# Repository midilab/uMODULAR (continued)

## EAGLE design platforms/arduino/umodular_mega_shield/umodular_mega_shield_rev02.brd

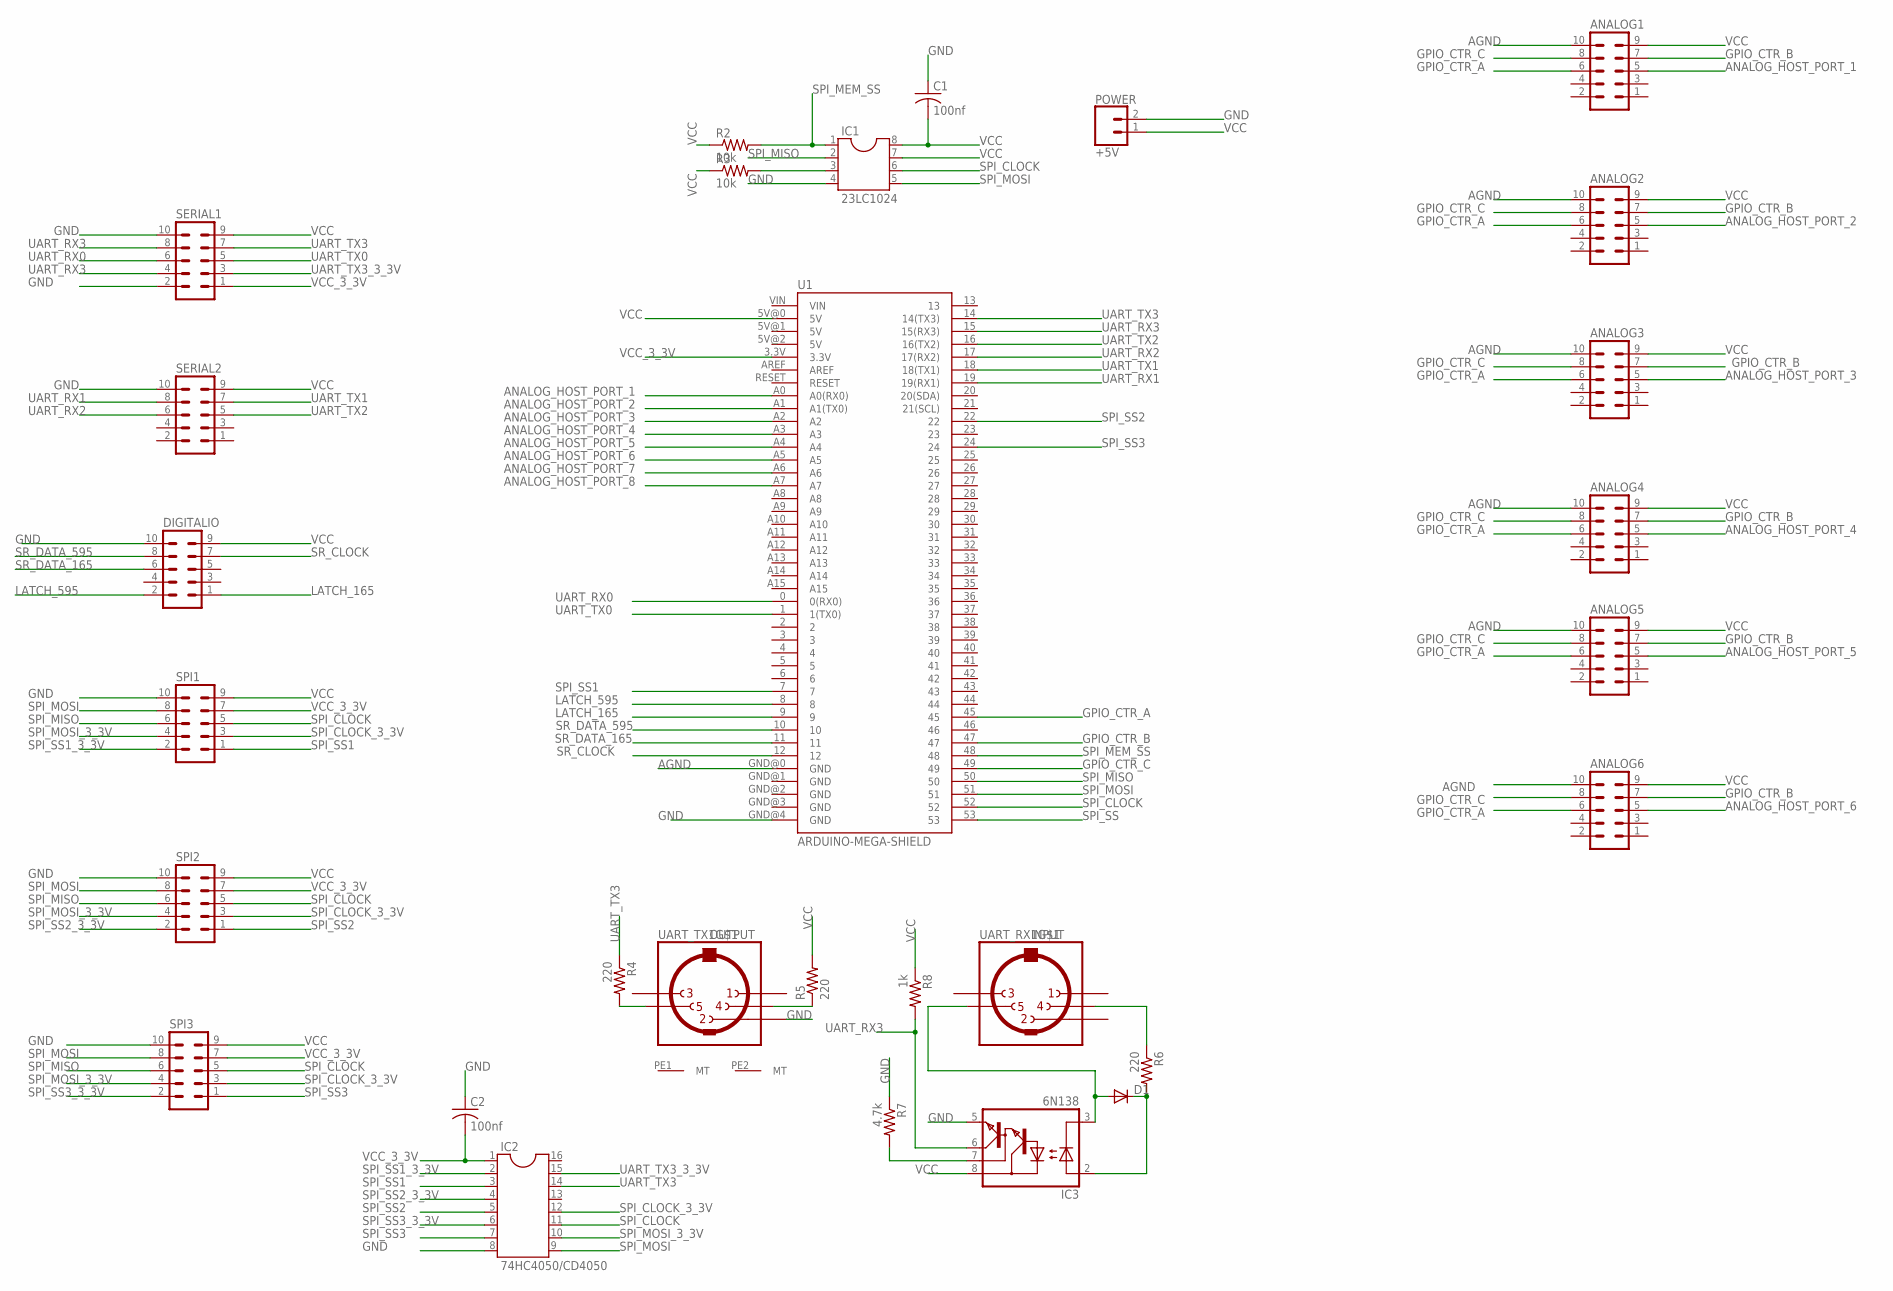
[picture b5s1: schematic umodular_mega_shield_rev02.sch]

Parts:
ANALOG1, ANALOG2, ANALOG3, ANALOG4, ANALOG5, ANALOG6: MA05-2
C1, C2: 100nf; C050-024X044
D1: 1N4148DO35-7; DO35-7
DIGITALIO: MA05-2
IC1: 23LC1024; DIL08
IC2: 74HC4050/CD4050; DIL16
IC3: 6N138; DIL08
POWER: +5V; 1X02_LOCK_LONGPADS
R2, R3: 10k; 0204/7@1
R4, R5, R6: 220; 0204/7@1
R7: 4.7k; 0204/7@1
R8: 1k; 0204/7@1
SERIAL1, SERIAL2: MA05-2
SPI1, SPI2, SPI3: MA05-2
U1: ARDUINO-MEGA-SHIELD; ARDUINO_MEGA@1
UART_RX1: INPUT; CP-2350
UART_TX1: OUTPUT; CP-2350

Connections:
AGND: ANALOG1.10, ANALOG2.10, ANALOG3.10, ANALOG4.10, ANALOG5.10, ANALOG6.10, U1.GND@0 (GND)
ANALOG_HOST_PORT_1: ANALOG1.5, U1.A0 (A0(RX0))
ANALOG_HOST_PORT_2: ANALOG2.5, U1.A1 (A1(TX0))
ANALOG_HOST_PORT_3: ANALOG3.5, U1.A2
ANALOG_HOST_PORT_4: ANALOG4.5, U1.A3
ANALOG_HOST_PORT_5: ANALOG5.5, U1.A4
ANALOG_HOST_PORT_6: ANALOG6.5, U1.A5
ANALOG_HOST_PORT_7: U1.A6
ANALOG_HOST_PORT_8: U1.A7
GND: C1.1, C2.1, DIGITALIO.10, IC1.4, IC2.8, IC3.5 (GND), POWER.2, R7.1, SERIAL1.2, SERIAL1.10, SERIAL2.10, SPI1.10, SPI2.10, SPI3.10, U1.GND@4 (GND), UART_TX1.2
GPIO_CTR_A: ANALOG1.6, ANALOG2.6, ANALOG3.6, ANALOG4.6, ANALOG5.6, ANALOG6.6, U1.45
GPIO_CTR_B: ANALOG1.7, ANALOG2.7, ANALOG3.7, ANALOG4.7, ANALOG5.7, ANALOG6.7, U1.47
GPIO_CTR_C: ANALOG1.8, ANALOG2.8, ANALOG3.8, ANALOG4.8, ANALOG5.8, ANALOG6.8, U1.49
LATCH_165: DIGITALIO.1, U1.9
LATCH_595: DIGITALIO.2, U1.8
unnamed: R5.1, UART_TX1.4
unnamed: R4.2, UART_TX1.5
unnamed: IC1.3, R3.2
unnamed: R6.1, UART_RX1.4
unnamed: D1.C, IC3.2 (A), R6.2
unnamed: D1.A, IC3.3 (C), UART_RX1.5
unnamed: IC3.7 (VB), R7.2
SPI_CLOCK: IC1.6, IC2.11, SPI1.5, SPI2.5, SPI3.5, U1.52
SPI_CLOCK_3_3V: IC2.12, SPI1.3, SPI2.3, SPI3.3
SPI_MEM_SS: IC1.1, R2.2, U1.48
SPI_MISO: IC1.2, SPI1.6, SPI2.6, SPI3.6, U1.50
SPI_MOSI: IC1.5, IC2.9, SPI1.8, SPI2.8, SPI3.8, U1.51
SPI_MOSI_3_3V: IC2.10, SPI1.4, SPI2.4, SPI3.4
SPI_SS: U1.53
SPI_SS1: IC2.3, SPI1.1, U1.7
SPI_SS1_3_3V: IC2.2, SPI1.2
SPI_SS2: IC2.5, SPI2.1, U1.22
SPI_SS2_3_3V: IC2.4, SPI2.2
SPI_SS3: IC2.7, SPI3.1, U1.24
SPI_SS3_3_3V: IC2.6, SPI3.2
SR_CLOCK: DIGITALIO.7, U1.12
SR_DATA_165: DIGITALIO.6, U1.11
SR_DATA_595: DIGITALIO.8, U1.10
UART_RX0: SERIAL1.6, U1.0 (0(RX0))
UART_RX1: SERIAL2.8, U1.19 (19(RX1))
UART_RX2: SERIAL2.6, U1.17 (17(RX2))
UART_RX3: IC3.6 (VO), R8.2, SERIAL1.4, SERIAL1.8, U1.15 (15(RX3))
UART_TX0: SERIAL1.5, U1.1 (1(TX0))
UART_TX1: SERIAL2.7, U1.18 (18(TX1))
UART_TX2: SERIAL2.5, U1.16 (16(TX2))
UART_TX3: IC2.14, R4.1, SERIAL1.7, U1.14 (14(TX3))
UART_TX3_3_3V: IC2.15, SERIAL1.3
VCC: ANALOG1.9, ANALOG2.9, ANALOG3.9, ANALOG4.9, ANALOG5.9, ANALOG6.9, C1.2, DIGITALIO.9, IC1.7, IC1.8, IC3.8 (VCC), POWER.1, R2.1, R3.1, R5.2, R8.1, SERIAL1.9, SERIAL2.9, SPI1.9, SPI2.9, SPI3.9, U1.5V@0 (5V)
VCC_3_3V: C2.2, IC2.1, SERIAL1.1, SPI1.7, SPI2.7, SPI3.7, U1.3.3V

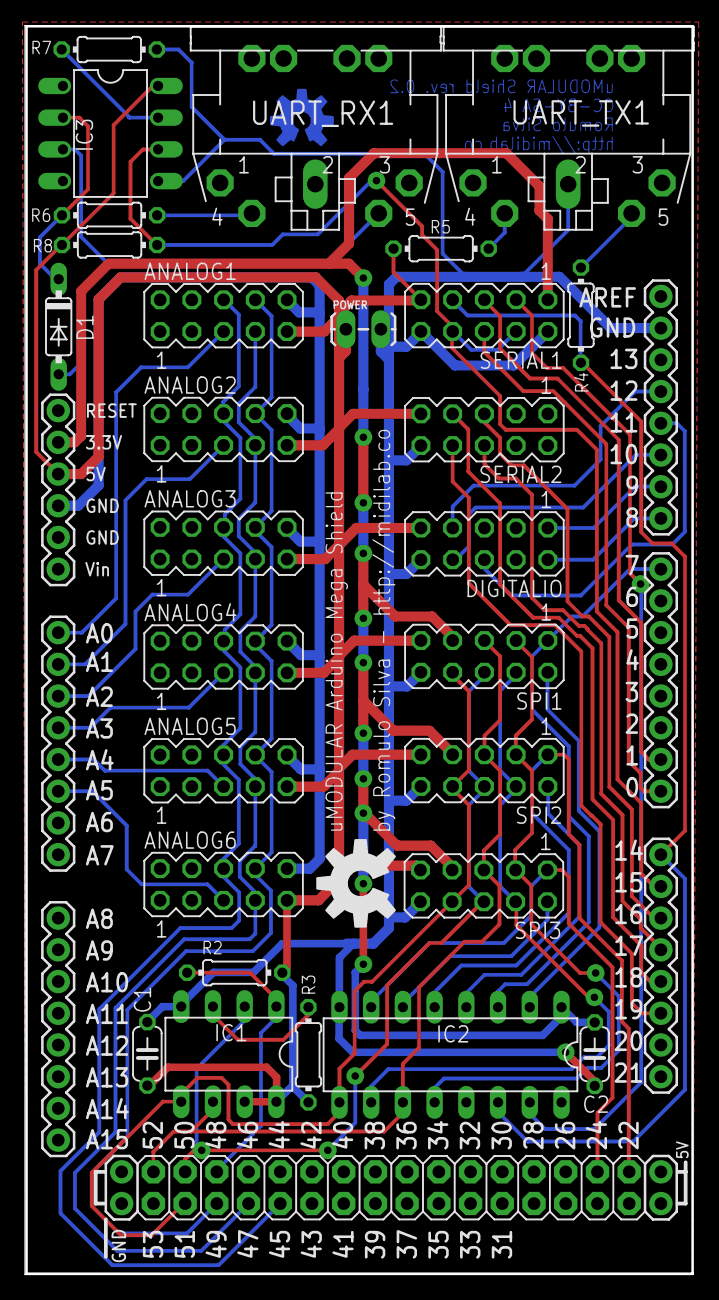
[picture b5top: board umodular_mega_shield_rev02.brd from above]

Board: 2 copper layers, 53.5 x 100.0 mm, 31 parts (0 on the bottom side), 46 nets.

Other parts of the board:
U$1: OSHW-LOGO-M
U$5: OSHW-LOGO-L

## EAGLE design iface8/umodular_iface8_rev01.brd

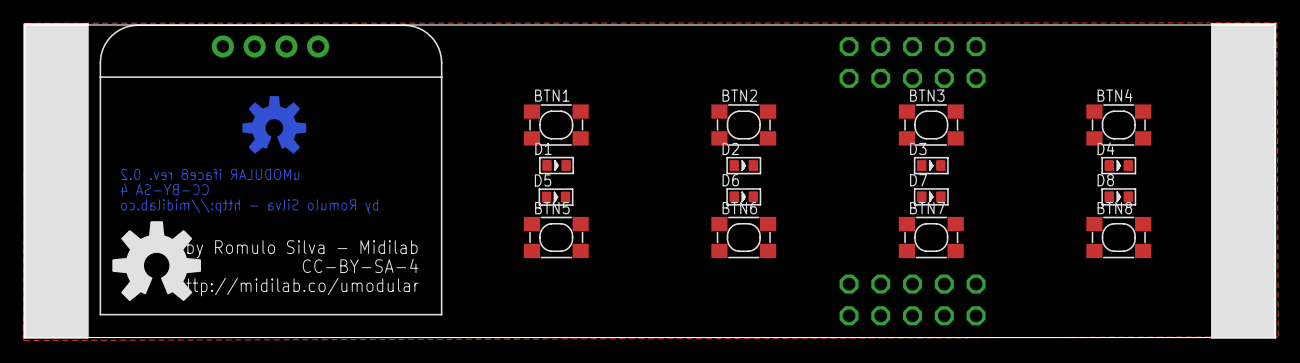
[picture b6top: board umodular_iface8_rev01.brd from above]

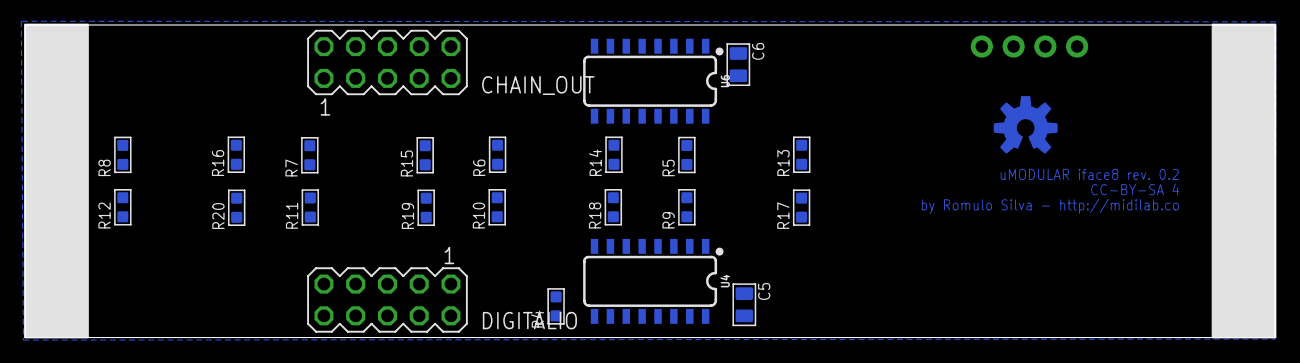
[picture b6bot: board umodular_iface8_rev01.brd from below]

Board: 2 copper layers, 100.0 x 25.0 mm, 44 parts (23 on the bottom side), 35 nets, no tracks yet.

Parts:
BTN1, BTN2, BTN3, BTN4, BTN5, BTN6, BTN7, BTN8: DHT-4235A; SW4-SMD-4.2X3.2X2.5MM
C5, C6: 100nf; C0805
CHAIN_OUT: MA05-2
D1, D2, D3, D4, D5, D6, D7, D8: RED-0603; LED-0603
DIGITALIO: MA05-2
R4, R5, R6, R7, R8, R9, R10, R11, R12: 10K; R0603
R13, R14, R15, R16, R17, R18, R19, R20: 220R; R0603
U4: SN74HC165DR; SO16
U6: SN74HC595D; SO16
U$1: OSHW-LOGO-M
U$2, U$4: OLED_0.96_I2C
U$3: OLED_0.96_I2C
U$5: OSHW-LOGO-L

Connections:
GND: BTN1.4, BTN2.4, BTN3.4, BTN4.4, BTN5.4, BTN6.4, BTN7.4, BTN8.4, C5.1, C6.2, CHAIN_OUT.10, D1.-, D2.-, D3.-, D4.-, D5.-, D6.-, D7.-, D8.-, DIGITALIO.10, U4.8, U4.15, U6.8, U6.13, U$3.GND
I2C_SCL: CHAIN_OUT.4, DIGITALIO.4, U$3.SCL
I2C_SDA: CHAIN_OUT.3, DIGITALIO.3, U$3.SDA
unnamed: BTN8.1, R12.1, U4.6
unnamed: R13.1, U6.15
unnamed: R14.1, U6.1
unnamed: R15.1, U6.2
unnamed: R16.1, U6.3
unnamed: R17.1, U6.4
unnamed: R18.1, U6.5
unnamed: BTN7.1, R11.1, U4.5
unnamed: BTN6.1, R10.1, U4.4
unnamed: BTN5.1, R9.1, U4.3
unnamed: BTN4.1, R8.1, U4.14
unnamed: BTN3.1, R7.1, U4.13
unnamed: BTN2.1, R6.1, U4.12
unnamed: BTN1.1, R5.1, U4.11
unnamed: R19.1, U6.6
unnamed: R20.1, U6.7
unnamed: D1.+, R13.2
unnamed: D2.+, R14.2
unnamed: D3.+, R15.2
unnamed: D4.+, R16.2
unnamed: D5.+, R17.2
unnamed: D6.+, R18.2
unnamed: D7.+, R19.2
unnamed: D8.+, R20.2
SPI_CLOCK: CHAIN_OUT.7, DIGITALIO.7, U4.2, U6.11
SPI_CS1: CHAIN_OUT.1, DIGITALIO.1, U4.1
SPI_CS2: CHAIN_OUT.2, DIGITALIO.2, U6.12
SPI_MISO: DIGITALIO.6, U4.9
SPI_MISO_CHAIN: CHAIN_OUT.6, R4.1, U4.10
SPI_MOSI: DIGITALIO.8, U6.14
SPI_MOSI_CHAIN: CHAIN_OUT.8, U6.9
VCC: C5.2, C6.1, CHAIN_OUT.9, DIGITALIO.9, R4.2, R5.2, R6.2, R7.2, R8.2, R9.2, R10.2, R11.2, R12.2, U4.16, U6.10, U6.16, U$3.VCC

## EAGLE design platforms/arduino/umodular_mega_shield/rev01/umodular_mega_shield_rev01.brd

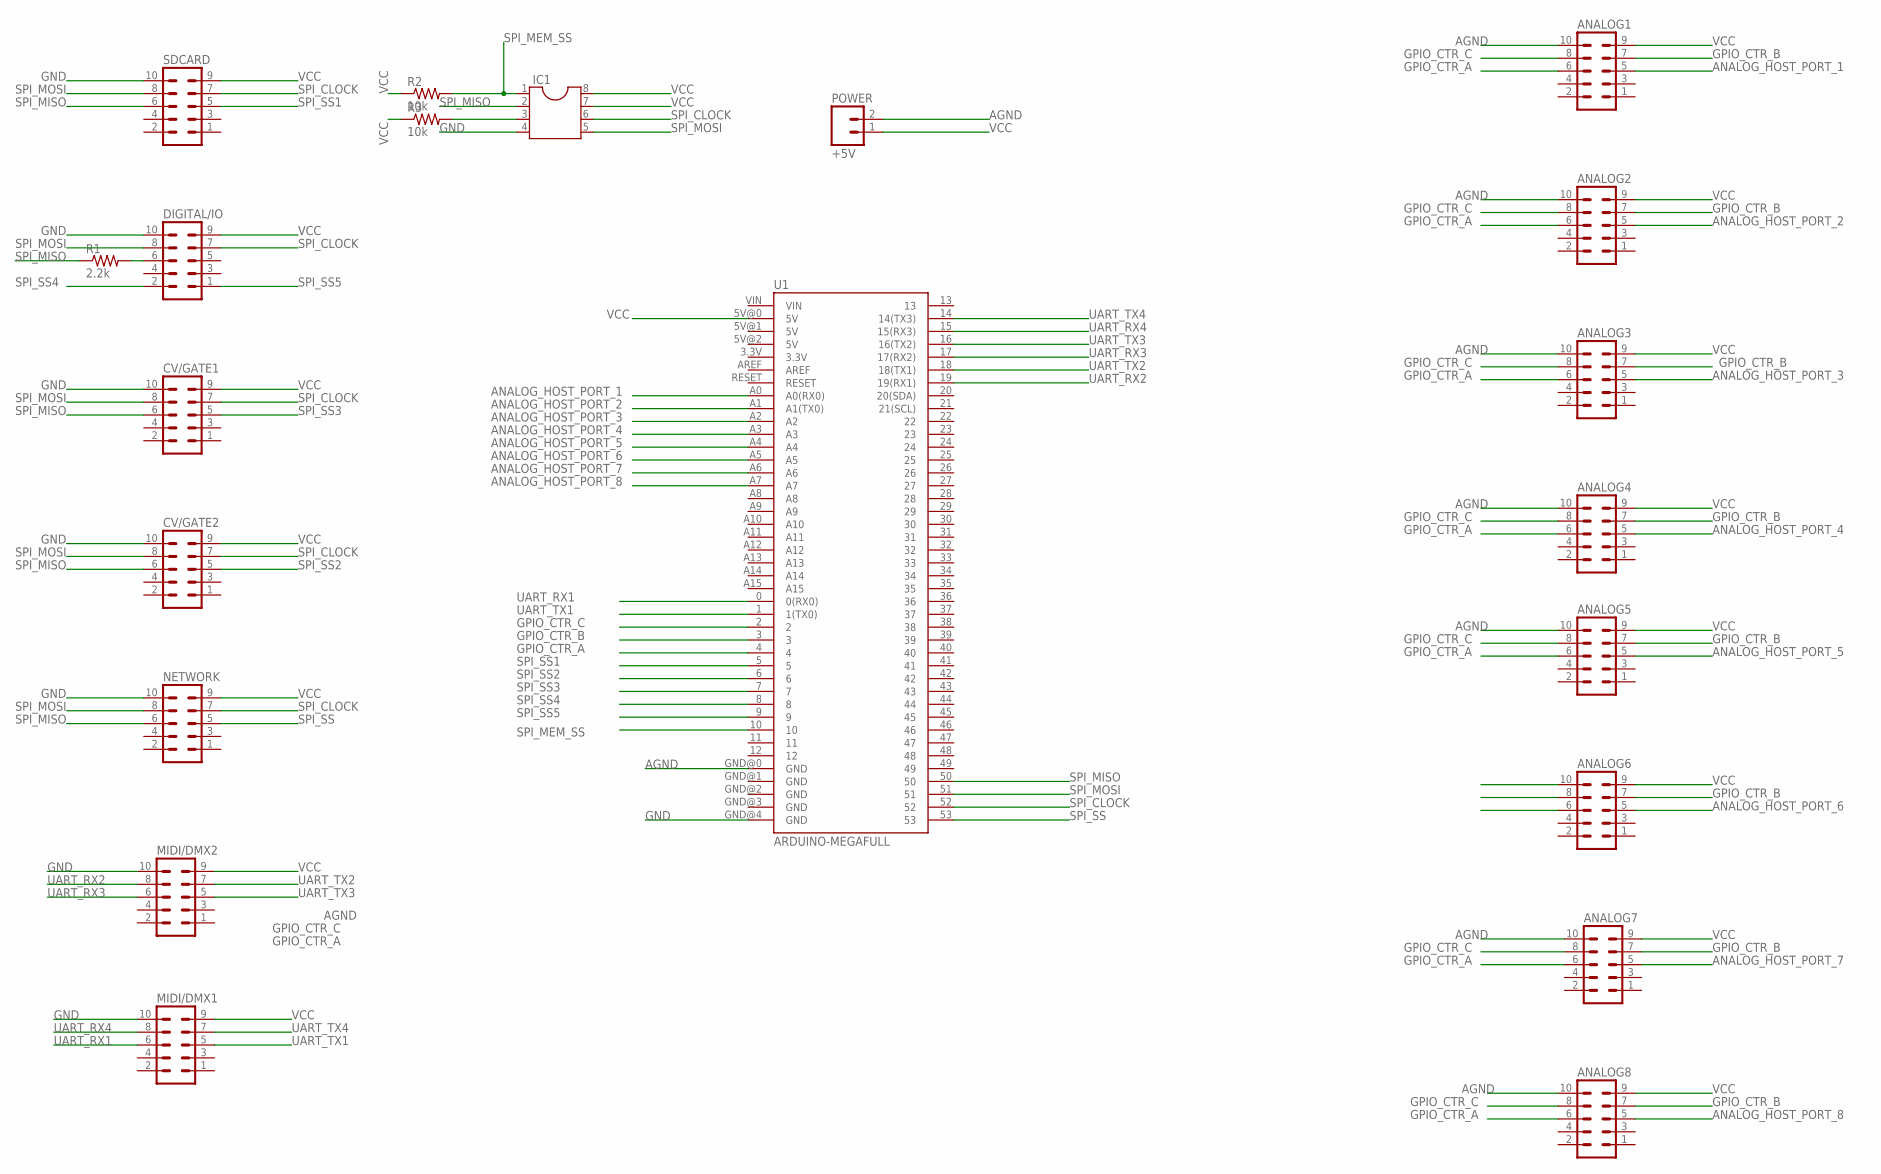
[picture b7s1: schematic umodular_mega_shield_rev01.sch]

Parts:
ANALOG1, ANALOG2, ANALOG3, ANALOG4, ANALOG5, ANALOG6, ANALOG7, ANALOG8: MA05-2
CV/GATE1, CV/GATE2: MA05-2
DIGITAL/IO: MA05-2
IC1: DIL8; DIL08
MIDI/DMX1, MIDI/DMX2: MA05-2
NETWORK: MA05-2
POWER: +5V; 1X02_LOCK_LONGPADS
R1: 2.2k; 0204/7
R2, R3: 10k; 0204/7
SDCARD: MA05-2
U1: ARDUINO-MEGAFULL; ARDUINO_MEGA

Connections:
AGND: ANALOG1.10, ANALOG2.10, ANALOG3.10, ANALOG4.10, ANALOG5.10, ANALOG6.10, ANALOG7.10, ANALOG8.10, POWER.2, U1.GND@0 (GND)
ANALOG_HOST_PORT_1: ANALOG1.5, U1.A0 (A0(RX0))
ANALOG_HOST_PORT_2: ANALOG2.5, U1.A1 (A1(TX0))
ANALOG_HOST_PORT_3: ANALOG3.5, U1.A2
ANALOG_HOST_PORT_4: ANALOG4.5, U1.A3
ANALOG_HOST_PORT_5: ANALOG5.5, U1.A4
ANALOG_HOST_PORT_6: ANALOG6.5, U1.A5
ANALOG_HOST_PORT_7: ANALOG7.5, U1.A6
ANALOG_HOST_PORT_8: ANALOG8.5, U1.A7
GND: CV/GATE1.10, CV/GATE2.10, DIGITAL/IO.10, IC1.4, MIDI/DMX1.10, MIDI/DMX2.10, NETWORK.10, SDCARD.10, U1.GND@4 (GND)
GPIO_CTR_A: ANALOG1.6, ANALOG2.6, ANALOG3.6, ANALOG4.6, ANALOG5.6, ANALOG6.6, ANALOG7.6, ANALOG8.6, U1.4
GPIO_CTR_B: ANALOG1.7, ANALOG2.7, ANALOG3.7, ANALOG4.7, ANALOG5.7, ANALOG6.7, ANALOG7.7, ANALOG8.7, U1.3
GPIO_CTR_C: ANALOG1.8, ANALOG2.8, ANALOG3.8, ANALOG4.8, ANALOG5.8, ANALOG6.8, ANALOG7.8, ANALOG8.8, U1.2
unnamed: DIGITAL/IO.6, R1.2
unnamed: IC1.3, R3.2
SPI_CLOCK: CV/GATE1.7, CV/GATE2.7, DIGITAL/IO.7, IC1.6, NETWORK.7, SDCARD.7, U1.52
SPI_MEM_SS: IC1.1, R2.2, U1.10
SPI_MISO: CV/GATE1.6, CV/GATE2.6, IC1.2, NETWORK.6, R1.1, SDCARD.6, U1.50
SPI_MOSI: CV/GATE1.8, CV/GATE2.8, DIGITAL/IO.8, IC1.5, NETWORK.8, SDCARD.8, U1.51
SPI_SS: NETWORK.5, U1.53
SPI_SS1: SDCARD.5, U1.5
SPI_SS2: CV/GATE2.5, U1.6
SPI_SS3: CV/GATE1.5, U1.7
SPI_SS4: DIGITAL/IO.2, U1.8
SPI_SS5: DIGITAL/IO.1, U1.9
UART_RX1: MIDI/DMX1.6, U1.0 (0(RX0))
UART_RX2: MIDI/DMX2.8, U1.19 (19(RX1))
UART_RX3: MIDI/DMX2.6, U1.17 (17(RX2))
UART_RX4: MIDI/DMX1.8, U1.15 (15(RX3))
UART_TX1: MIDI/DMX1.5, U1.1 (1(TX0))
UART_TX2: MIDI/DMX2.7, U1.18 (18(TX1))
UART_TX3: MIDI/DMX2.5, U1.16 (16(TX2))
UART_TX4: MIDI/DMX1.7, U1.14 (14(TX3))
VCC: ANALOG1.9, ANALOG2.9, ANALOG3.9, ANALOG4.9, ANALOG5.9, ANALOG6.9, ANALOG7.9, ANALOG8.9, CV/GATE1.9, CV/GATE2.9, DIGITAL/IO.9, IC1.7, IC1.8, MIDI/DMX1.9, MIDI/DMX2.9, NETWORK.9, POWER.1, R2.1, R3.1, SDCARD.9, U1.5V@0 (5V)

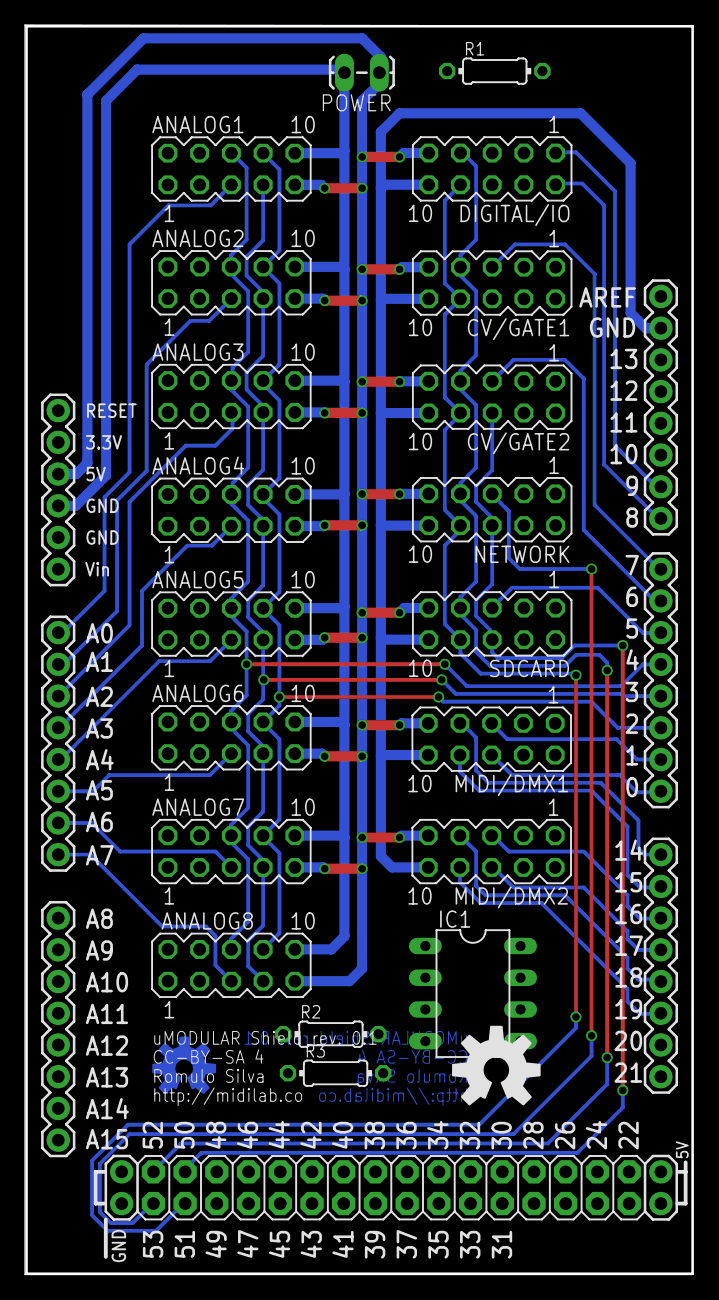
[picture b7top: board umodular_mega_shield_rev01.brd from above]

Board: 2 copper layers, 53.5 x 100.1 mm, 23 parts (0 on the bottom side), 34 nets.

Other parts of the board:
U$1: OSHW-LOGO-M
U$5: OSHW-LOGO-L

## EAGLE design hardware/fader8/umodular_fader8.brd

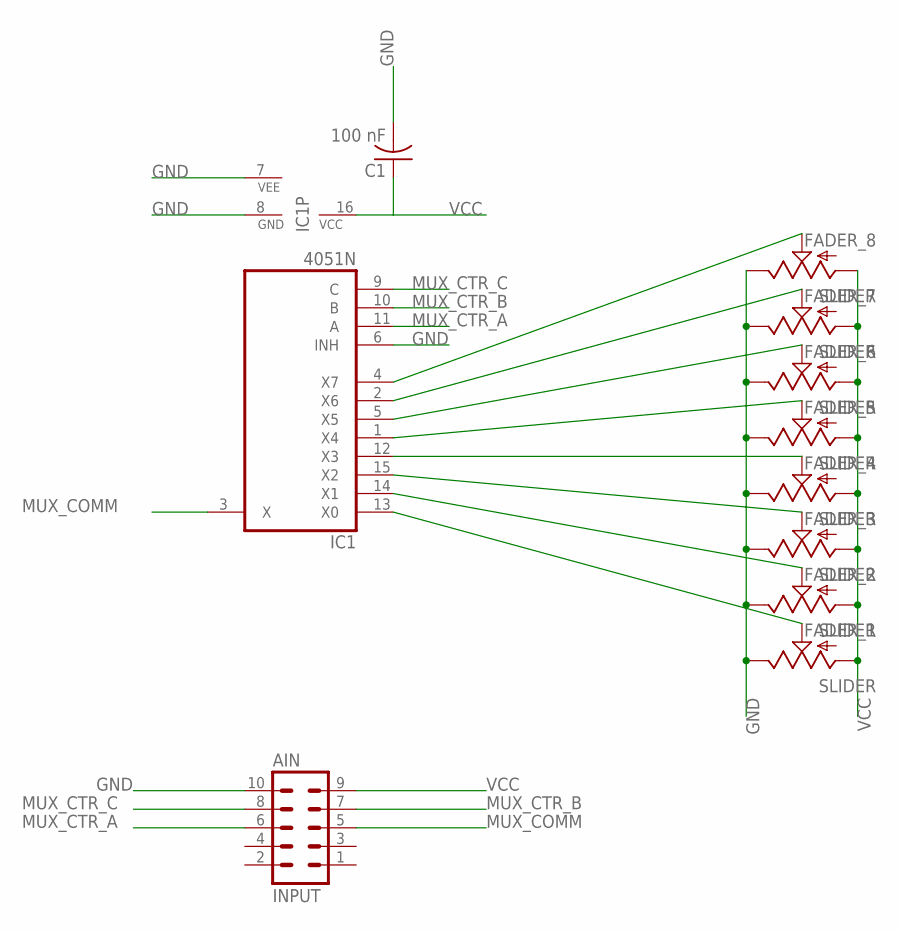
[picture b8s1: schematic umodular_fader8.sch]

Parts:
AIN: INPUT; MA05-2
C1: 100 nF; C050-024X044
FADER_1, FADER_2, FADER_3, FADER_4, FADER_5, FADER_6, FADER_7, FADER_8: SLIDER
IC1: 4051N; DIL16

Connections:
GND: AIN.10, C1.2, FADER_1.1 (E), FADER_2.1 (E), FADER_3.1 (E), FADER_4.1 (E), FADER_5.1 (E), FADER_6.1 (E), FADER_7.1 (E), FADER_8.1 (E), IC1.6 (INH), IC1.7 (VEE), IC1.8 (GND)
MUX_COMM: AIN.5, IC1.3 (X)
MUX_CTR_A: AIN.6, IC1.11 (A)
MUX_CTR_B: AIN.7, IC1.10 (B)
MUX_CTR_C: AIN.8, IC1.9 (C)
unnamed: FADER_1.2A (S), IC1.13 (X0)
unnamed: FADER_2.2A (S), IC1.14 (X1)
unnamed: FADER_3.2A (S), IC1.15 (X2)
unnamed: FADER_4.2A (S), IC1.12 (X3)
unnamed: FADER_5.2A (S), IC1.1 (X4)
unnamed: FADER_6.2A (S), IC1.5 (X5)
unnamed: FADER_7.2A (S), IC1.2 (X6)
unnamed: FADER_8.2A (S), IC1.4 (X7)
VCC: AIN.9, C1.1, FADER_1.3 (A), FADER_2.3 (A), FADER_3.3 (A), FADER_4.3 (A), FADER_5.3 (A), FADER_6.3 (A), FADER_7.3 (A), FADER_8.3 (A), IC1.16 (VCC)

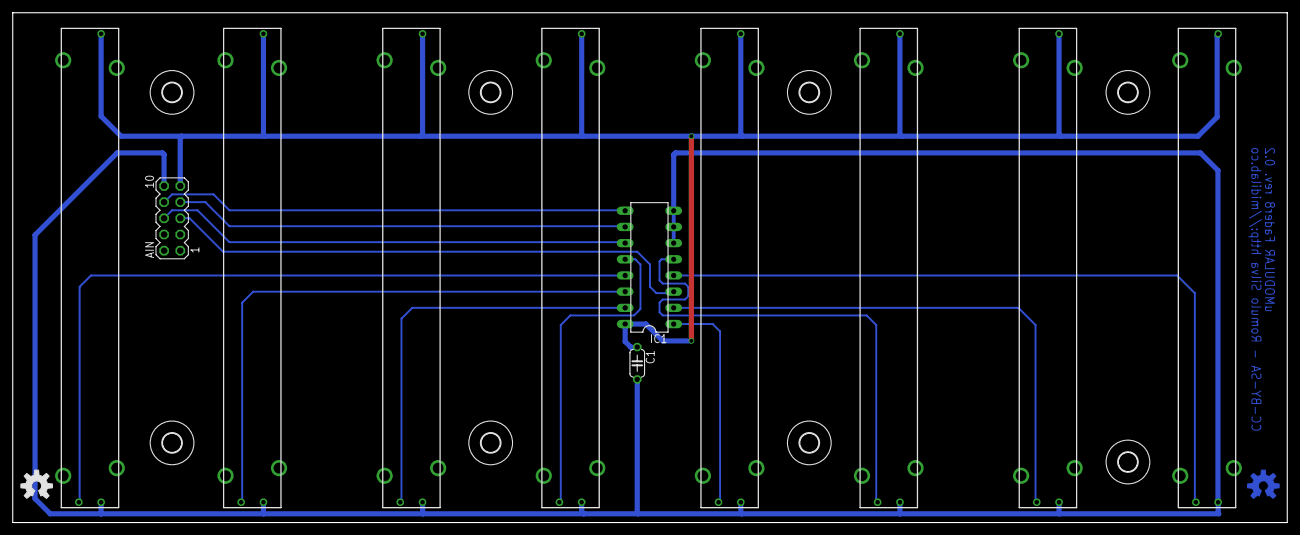
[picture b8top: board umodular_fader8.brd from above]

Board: 2 copper layers, 200.0 x 80.0 mm, 21 parts (0 on the bottom side), 14 nets.

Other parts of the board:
U$1, U$2, U$3, U$4, U$5, U$6, U$7, U$8: 3,0
U$9, U$10: OSHW-LOGO-M

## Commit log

2015-10-14 Create README.md
    First notes about the project
2015-10-19 Clock library version 1.0 added
2015-10-19 Update README.md with some notes about Clock library. Added default initial dirs structure
2015-10-22 Added arduino Micro and Mini Hardware files rev. 0.1
2015-10-22 Added general license for all hardware files inside hardware directory - CC-BY-SA 4.0
2015-10-22 Added notes and visual reference for Arduino micro and mini shiled
2015-10-23 Fader8 Release rev. 0.1
2015-10-23 README notes about Fader8
2015-10-23 Pot8 Release rev. 0.1
2015-10-23 README notes about Pot8
2015-10-23 Midi4 Release rev. 0.1
2015-10-23 README notes about Midi4
2015-10-24 README update notes
2015-12-07 Fix arduino micro/mini shiled size to fixed 10x5cm
2015-12-07 Fix module Pot8 size to fixed 10x2.5cm
2015-12-07 Fix module Fader8 size to fixed 20x8cm
2017-05-12 Subdividing uMODULAR into hardware and libraries repository. Cleaning for new repository strucuture.
2017-05-12 Adding CC-BY-SA 4 as main License for all hardware schematics and boards
2017-05-12 Adding the Revision 2 of Arduino Shield for Mega.
2017-05-12 Adding midi4 module Revision 2.
2017-05-12 Deleting revision 0.1 of umodular shield for arduino mega.
2017-05-12 Structuring directories
2017-05-16 >ctrl16 module working on...
2017-05-16 >mix4 module working on...
2017-05-16 >pot16 module working on...
2017-05-16 visual reference fix for png board view
2017-05-16 added top view of midi4 module pcb
2017-05-16 added platform arduino mega shiled a external power connector.
2017-05-17 ctrl16 revision 0.1
2017-05-17 midi4 revision 0.2
2017-05-17 mix4 revision 01
2017-05-17 platform arduino mega shield revision 02
2017-05-17 pot16 revision 01
2017-05-17 updating project description
2017-05-17 updating ctrl16 module description
2017-05-17 updating mix4 module description
2017-05-17 updating pot16 module description
2017-05-17 updating uMODULAR Arduino Mega Shield project description
2017-05-17 updating midi4 module description
2017-05-17 updating ctrl16 BOM list
2017-05-17 updating mix4 BOM list
2017-05-17 updating pot16 BOM list
2017-05-17 updating midi4 BOM list
2017-05-17 updating platform arduino mega shield BOM list
2017-05-17 diagraming all README.md
2017-05-17 ctrl16 README.md diagraming update
2017-06-14 iface8: working on new module with oled 0.96 support.
2017-06-14 iface8: align components.
2017-06-14 brain8: A 8 bits controlled uMODULAR main brain. Arduino Mega version. Starting Alignment of components
2017-06-14 iface8: ready to route boy!
2017-06-14 iface8: final oled adjustment
2017-10-02 Change shift registers from SPI hardware based to Software implementation. Free the SPI bus for things more important(SDCARD and RAM)
2017-10-12 changes that reflects main hardware connections of project. Hardware SPI are only for RAM memory, sdcard goes via SoftSPI(exclusive wire path) and shift registers 165 and 595 goes via shiftIn and shi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
2021-04-13 fix bounrs fader part. swaped pin 2 and 1.
2023-02-03 move old v1 to a archive folder
2023-02-03 added kicad library for umodular subsystems for reuse on other projects and main repo for maitain and updates
2023-02-03 revert arduino mega shiled back to make use of SPI on shared subsystem
2023-02-03 update sheets description and main pdf with all libs
2023-02-04 added uctrl reference to readme
2023-02-04 added reference to aciduino v2 as umodular app
2023-02-06 update README images references
2023-02-06 typo on image path fix
2023-03-14 added per module pdf schematic
2023-06-06 update README notes
2023-06-06 fix image of umodular v2 series
2023-06-06 fix md formating
2023-06-06 V1 information added
